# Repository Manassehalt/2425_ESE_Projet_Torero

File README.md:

# 2425_ESE_Projet_Torero

Projet de 3ème année d'ESE réalisé par :  
- **JACQUOT Nolan**  
- **GUIFFAULT Gabriel**  
- **BOULOT Paul**  
- **THOMAR Jean-Philippe**

Ce projet consiste à concevoir un robot autonome de A à Z, combinant électronique et programmation, pour jouer une partie de "chat et souris".

---

## Cahier des charges:
> [!IMPORTANT]
>- Le robot doit être capable de se déplacer sur une table sans tomber (absence de bord et de marquage)
>- Le robot doit être capable de détecter l'autre robot présent sur la table pour le fuir ou le chasser en fonction de son rôle dans la partie.
>- Le robot doit être capable de détecter un contact, même léger, avec le robot adverse et changer son comportement d'un rôle vers l'autre.

Objectif annexe:
- Le robot peut réaliser une odométrie simple pour suivre le bord de table lorsqu'il débute en souris
- Le robot peut réaliser une odométrie simple pour se positionner au centre de la table avant de commencer la traque lorsqu'il débute en chat
- Le robot peut déclencher un brusque changement de direction s'il détecte un robot approchant rapidement en mode souris
- Le robot peut effectuer des prédictions de trajectoire et effectuer des trajectoires de collision en prévision du deplacement adverse en mode chat
- Le robot évite de prendre des directions ou il serait acculé dans un angle de table

## Architecture du système

[Schéma architectural](https://github.com/user-attachments/files/17220902/Schema.architectural.pdf)

1. **Détection de l'environnement** :
   - Les **capteurs de bord** détectent les limites de la table pour prévenir les chutes.
   - Le **LIDAR** identifie et localise les robots adverse.
   - La **centrale inertielle** mesure les mouvements brusques et détecte les chocs pour changer l'état, chat ou souris, du robot.

2. **Traitement des données** :
   - Le **microcontrôleur** centralise les informations provenant des capteurs, analyse les données et décide des actions en fonction du rôle actuel du robot (chat ou souris).

3. **Actionneur** :
   - Les moteurs sont contrôlés via un système de quadrants.
   - Le microcontrôleur ajuste les commandes de mouvement en temps réel (éviter les chutes, fuir ou poursuivre le robot adverse).

4. **Comportement interactif** :
   - Un **switch de comportement** permet de basculer entre les rôles de "chat" et "souris".
   - Les **LED de debug** affichent des informations sur l'état et le rôle actuel du robot.

5. **Alimentation** :
   - Une **batterie** alimente l'ensemble du système.
   - Des convertisseurs intégrés fournissent les tensions nécessaires (7,2 V, 5 V et 3,3 V) pour les différents composants.

## Environnement:

> [!IMPORTANT]
> Table de 200cm x 160cm
> 
> Table sans bords ni marquages!
> 
> Robot assimilable à un cylindre de 17 cm de diametre et 15 cm de hauteur 

##  Liens utiles

### Documentation et ressources :
- [Datasheets](https://github.com/Manassehalt/2425_ESE_Projet_Torero/tree/main/Datasheet)  
- [Liste des tâches](https://github.com/Manassehalt/2425_ESE_Projet_Torero/blob/main/Calculs%20et%20brouillons/Remarque_Sch.md)  
- [BOM (Bill of Materials)](https://github.com/Manassehalt/2425_ESE_Projet_Torero/blob/main/BOM.xlsx)
  
### Design électronique :
- [Fichiers PCB](https://github.com/Manassehalt/2425_ESE_Projet_Torero/tree/main/PCB)  
- [Schémas KiCad](https://github.com/Manassehalt/2425_ESE_Projet_Torero/blob/main/PCB/Projet_torero/Projet_torero.kicad_sch)  

### Code STM32 :
- [Dossier code](https://github.com/Manassehalt/2425_ESE_Projet_Torero/tree/main/Projet_ESE_STM32)  

---

### Aperçu de la carte PCB

[Voir le modèle en 3D](https://github.com/Manassehalt/2425_ESE_Projet_Torero/blob/main/Graphique_Logo/PCB%20carte%203d.PNG)  

### Calculs et développement

- [Dossier calculs](https://github.com/Manassehalt/2425_ESE_Projet_Torero/tree/8892ed05e16a1e8a040fe9dc08f957ab23dc9e8/Calculs%20et%20brouillons)

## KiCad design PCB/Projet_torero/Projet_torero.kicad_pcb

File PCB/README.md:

# Partie PCB - Projet Torero

Ce projet utilise **KiCad** pour la conception des schémas et des PCB. L'architecture électronique est organisée de manière hiérarchique pour une gestion claire.

---

##  Organisation des fichiers
La hiérarchie des schémas est structurée en plusieurs pages, chacune correspondant à une fonctionnalité spécifique :

- **Page principale (Racine)** : Vue d'ensemble de l'architecture.
- **STM32 (Page 2)** : Microcontrôleur central et ses connexions.
- **Puissance (Page 3)** : Alimentation et distribution des tensions.
  - Contrôle des moteurs gauche et droit.
- **Capteurs (Page 4)** : Intégration des capteurs, tels que le Lidar, l'accéléromètre, et les détecteurs de bord.
- **Alimentation (Page 5)** : Régulateurs pour les tensions de 3,3 V et 5 V.

---

## Composants principaux

### **Microcontrôleur STM32** (Page 2)
- **STM32G431CBU** : Le contrôle central du système.
- Connexions UART, SPI, et GPIO configurées pour communiquer avec les capteurs, moteurs, et périphériques.

### **Puissance et Moteurs** (Pages 3, 6, 7)
- **Drivers moteurs ZXBM5210-SP** pour le contrôle des moteurs gauche et droit.
- Les connecteurs moteurs incluent des signaux pour les encodeurs et les commandes de direction.

### **Capteurs** (Page 4)
- **Lidar** : Connecté via UART pour les mesures de distance et d'obstacles.
- **Accéléromètre ADXL343** : Géré via SPI pour les données inertiales.
- **Capteurs de bord QRD1114** : Utilisés pour détecter les limites de la table.

### **Alimentation** (Page 5)
- Régulateur **5 V** : MP14755.
- Régulateur **3,3 V** : BU33SD5WG-TR.
- Connecteurs pour la batterie 7,2 V et le switch ON/OFF.

---

## Fonctionnalités de conception
- **Hiérarchie des schémas** : Organisation pour une meilleure lisibilité.
- **Test points** : Ajoutés pour faciliter les mesures et le debug sur le PCB avec l'ocsilloscope.

---

## Aperçu des schémas

### Vue principale

### STM32

### Puissance

Voici le schéma d'un des moteurs :

### Capteurs

Voici le schéma d'un des caepterus de bord :

### Alimentation

---

## Rutage du PCB :

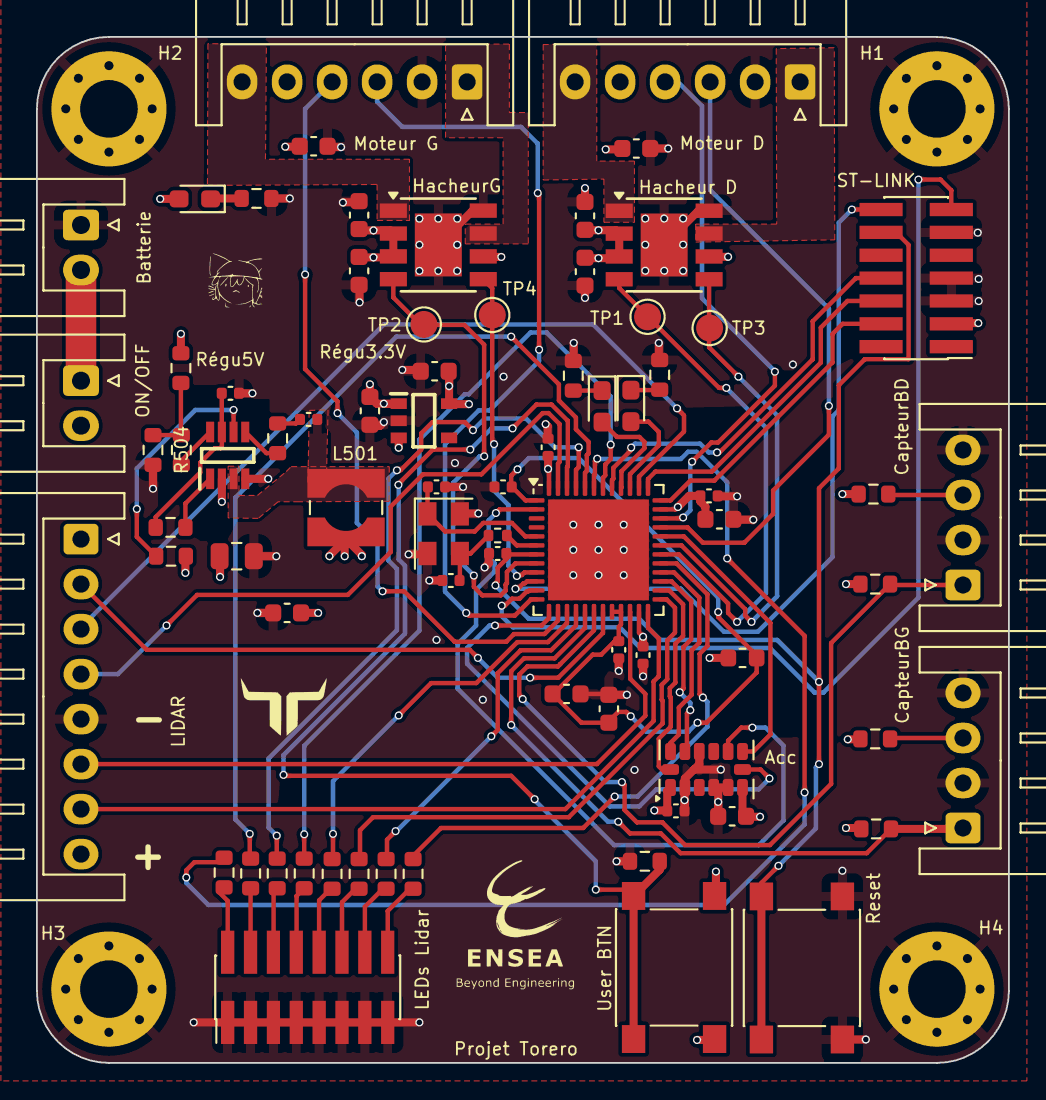
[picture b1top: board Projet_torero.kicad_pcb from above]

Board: 4 copper layers, 54.0 x 57.0 mm, 79 parts (0 on the bottom side), 72 nets.

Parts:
10k201: 10k; R_0603_1608Metric
Acc: ADXL343; LGA-14_3x5mm_P0.8mm_LayoutBorder1x6y
Batterie: Conn_01x02; JST_XH_S2B-XH-A_1x02_P2.50mm_Horizontal
C201, C202: 20p; C_0402_1005Metric
C203, C204, C206, C207, C208, C402, C502, C503: 100n; C_0402_1005Metric
C205, C210, C401, C505, C506, C601, C603, C701, C703: 1u; C_0603_1608Metric
C209: 4n7; C_0603_1608Metric
C211: 10n; C_0402_1005Metric
C501: 22u; C_0805_2012Metric
C504: 47u; C_0603_1608Metric
C602, C702: 10u; C_0603_1608Metric
CapteurBD: JST_XH_S4B-XH-A_1x04_P2.50mm_Horizontal
CapteurBG: JST_XH_S4B-XH-A_1x04_P2.50mm_Horizontal
D1, D202: Red; LED_0603_1608Metric_Pad1.05x0.95mm_HandSolder
D201: Green; LED_0603_1608Metric_Pad1.05x0.95mm_HandSolder
H1, H2, H3, H4: MountingHole_Pad; MountingHole_3.2mm_M3_Pad_Via
Hacheur D: ZXBM5210-SP; Diodes_SO-8EP
HacheurG: ZXBM5210-SP; Diodes_SO-8EP
L202: L; L_0603_1608Metric
L501: 4u7; L_Wuerth_WE-TPC-3816
LEDs Lidar: Conn_02x08_Odd_Even; PinHeader_2x08_P1.27mm_Vertical_SMD
LIDAR: Conn_01x08; JST_XH_S8B-XH-A_1x08_P2.50mm_Horizontal
Moteur D: Conn_01x06; JST_XH_S6B-XH-A_1x06_P2.50mm_Horizontal
Moteur G: Conn_01x06; JST_XH_S6B-XH-A_1x06_P2.50mm_Horizontal
ON/OFF: Conn_01x02; JST_XH_S2B-XH-A_1x02_P2.50mm_Horizontal
R201: 10; R_0402_1005Metric
R202: 120; R_0603_1608Metric
R203, R314: 140; R_0603_1608Metric
R204, R205, R206, R207, R208, R209, R210, R211: 1k; R_0603_1608Metric
R501, R502: 100k; R_0603_1608Metric
R503: 20; R_0603_1608Metric
R504: 16k; R_0603_1608Metric
R505: 40k2; R_0603_1608Metric
R506: 7k68; R_0603_1608Metric
R801, R901: 300; R_0603_1608Metric
R802, R902: 15k3; R_0603_1608Metric
Reset: SW_Push; SW_Push_1P1T_NO_6x6mm_H9.5mm
Régu3.3V: BU33SD5WG-TR; SOT95P280X125-5N
Régu5V: MP1475SGJ-P; SOT65P280X100-8N
ST-LINK: Conn_02x07_Odd_Even; PinHeader_2x07_P1.27mm_Vertical_SMD
SW201: SW_Push; SW_Push_1P1T_NO_6x6mm_H9.5mm
TP1, TP2, TP3, TP4: TestPoint; TestPoint_Pad_D1.5mm
U201: STM32G431CBUx; QFN-48-1EP_7x7mm_P0.5mm_EP5.6x5.6mm
Y201: Crystal_GND24_Small; Crystal_SMD_EuroQuartz_MT-4Pin_3.2x2.5mm

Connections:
7.2V: C501.1, C601.2, C602.1, C701.2, C702.1, Hacheur D.2 (VM), Hacheur D.3 (VDD), Hacheur D.6 (VREF), HacheurG.2 (VM), HacheurG.3 (VDD), HacheurG.6 (VREF), ON/OFF.2, R501.1, Régu5V.2 (IN)
+3.3V: Acc.1 (Vdd_I/O), Acc.6 (Vs), C206.1, C207.1, C208.1, C209.1, C401.1, C402.2, C506.2, C603.2, C703.2, D201.2 (A), L202.1, Moteur D.5, Moteur G.5, R801.1, R802.2, R901.1, R902.2, Régu3.3V.5 (VOUT), ST-LINK.3, SW201.2, U201.23 (VDD), U201.35 (VDD), U201.48 (VDD)
+5V: C504.1, C505.1, L501.2, LIDAR.8, R505.1, Régu3.3V.1 (VIN), Régu3.3V.3 (STBY)
/ALIMENTATION/Sortie Régulateur 5V: C503.2, L501.1, Régu5V.3 (SW)
/CAPTEURS/ANALOG_OUTPUT_CAPT_BORD_D: CapteurBD.1, R901.2, U201.18 (PB1)
/CAPTEURS/ANALOG_OUTPUT_CAPT_BORD_G: CapteurBG.1, R801.2, U201.17 (PB0)
/CAPTEURS/CS_ACC: Acc.7 (~CS), U201.13 (PA5)
/CAPTEURS/DEV_EN_LIDAR: LIDAR.3, U201.38 (PA15)
/CAPTEURS/INT1_ACC: Acc.8 (INT1), U201.32 (PA10)
/CAPTEURS/INT2_ACC: Acc.9 (INT2), U201.2 (PC13)
/CAPTEURS/M_EN_LIDAR: LIDAR.2, U201.19 (PB2)
/CAPTEURS/M_SCTR_LIDAR: LIDAR.4, U201.47 (PB9)
/CAPTEURS/Rx_LIDAR: LIDAR.6, U201.22 (PB10)
/CAPTEURS/SCLK_ACC: Acc.14 (SCL/SCLK), U201.26 (PB13)
/CAPTEURS/SDI_ACC: Acc.13 (SDA/SDI/SDIO), U201.28 (PB15)
/CAPTEURS/SDO_ACC: Acc.12 (SDO/ADDR), U201.27 (PB14)
/CAPTEURS/Tx_LIDAR: LIDAR.7, U201.24 (PB11)
/PUISSANCE/EncodeurA_Droite: Moteur G.3, U201.12 (PA4)
/PUISSANCE/EncodeurA_Gauche: Moteur D.3, U201.33 (PA11)
/PUISSANCE/EncodeurB_Droite: Moteur G.4, U201.14 (PA6)
/PUISSANCE/EncodeurB_Gauche: Moteur D.4, U201.34 (PA12)
/PUISSANCE/FWDD: HacheurG.4 (FWD), TP2.1, U201.8 (PA0)
/PUISSANCE/FWDG: Hacheur D.4 (FWD), TP1.1, U201.30 (PA8)
/PUISSANCE/Moteur1/Commande moteur: HacheurG.7 (OUT2), Moteur G.1
/PUISSANCE/Moteur1/Connecteur Moteur: HacheurG.1 (OUT1), Moteur G.6
/PUISSANCE/Moteur/Commande moteur: Hacheur D.7 (OUT2), Moteur D.1
/PUISSANCE/Moteur/Connecteur Moteur: Hacheur D.1 (OUT1), Moteur D.6
/PUISSANCE/REVD: HacheurG.5 (REV), TP4.1, U201.9 (PA1)
/PUISSANCE/REVG: Hacheur D.5 (REV), TP3.1, U201.31 (PA9)
/STM32/USER_BTN: 10k201.2, SW201.1, U201.46 (PB8)
GND: 10k201.1, Acc.2 (GND), Acc.4 (GND), Acc.5 (GND), Acc.11 (RES), Batterie.1, C201.1, C202.2, C203.2, C204.2, C205.2, C206.2, C207.2, C208.2, C209.2, C210.2, C211.2, C401.2, C402.1, C501.2, C502.2, C504.2, C505.2, C506.1, C601.1, C602.2, C603.1, C701.1, C702.2, C703.1, CapteurBD.2, CapteurBD.4, CapteurBG.2, CapteurBG.4, H1.1, H2.1, H3.1, H4.1, Hacheur D.8 (GND), Hacheur D.9 (GND), HacheurG.8 (GND), HacheurG.9 (GND), LEDs Lidar.1, LEDs Lidar.3, LEDs Lidar.5, LEDs Lidar.7, LEDs Lidar.9, LEDs Lidar.11, LEDs Lidar.13, LEDs Lidar.15, LIDAR.5, Moteur D.2, Moteur G.2, R202.1, R203.1, R314.1, R506.2, Reset.1, Régu3.3V.2 (GND), Régu5V.4 (GND), ST-LINK.5, ST-LINK.7, ST-LINK.11, U201.49 (VSS), Y201.2, Y201.4
LED_E: R205.1, U201.44 (PB6)
LED_N: R204.1, U201.43 (PB5)
LED_NE: R208.1, U201.15 (PA7)
LED_NW: R209.1, U201.25 (PB12)
LED_S: R206.1, U201.45 (PB7)
LED_SE: R210.1, U201.16 (PC4)
LED_SW: R211.1, U201.29 (PC6)
LED_W: R207.1, U201.42 (PB4)
NRST: C203.1, Reset.2, ST-LINK.12, U201.7 (PG10)
unnamed: C201.2, R201.2, Y201.3
unnamed: C503.1, R503.1
unnamed: D1.1 (K), R314.2
unnamed: D201.1 (K), R202.2
unnamed: D202.1 (K), R203.2
unnamed: R503.2, Régu5V.5 (BST)
unnamed: R501.2, Régu5V.6 (EN/SYNC)
unnamed: R504.2, Régu5V.8 (FB)
unnamed: R502.2, Régu5V.1 (PG)
unnamed: C502.1, R502.1, Régu5V.7 (VCC)
unnamed: LEDs Lidar.2, R204.2
unnamed: LEDs Lidar.4, R205.2
unnamed: LEDs Lidar.6, R206.2
unnamed: LEDs Lidar.8, R207.2
unnamed: LEDs Lidar.10, R208.2
unnamed: LEDs Lidar.12, R209.2
unnamed: LEDs Lidar.14, R210.2
unnamed: LEDs Lidar.16, R211.2
unnamed: Batterie.2, ON/OFF.1
unnamed: CapteurBG.3, R802.1
unnamed: CapteurBD.3, R902.1
unnamed: R504.1, R505.2, R506.1
unnamed: C202.1, U201.5 (PF0), Y201.1
unnamed: R201.1, U201.6 (PF1)
unnamed: C204.1, C205.1, C210.1, C211.1, L202.2, U201.1 (VBAT), U201.20 (VREF+), U201.21 (VDDA)
STATUS_LED: D202.2 (A), U201.39 (PC10)
STATUS_LED_Debug: D1.2 (A), U201.40 (PC11)
SWCLK: ST-LINK.6, U201.37 (PA14)
SWDIO: ST-LINK.4, U201.36 (PA13)
SWO: ST-LINK.8, U201.41 (PB3)
VCP_RX: ST-LINK.13, U201.11 (PA3)
VCP_TX: ST-LINK.14, U201.10 (PA2)

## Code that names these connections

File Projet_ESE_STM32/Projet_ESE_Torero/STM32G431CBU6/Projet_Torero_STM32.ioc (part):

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Mcu.Name=STM32G431C(6-8-B)Ux
Mcu.Package=UFQFPN48
Mcu.UserName=STM32G431CBUx
PA0.Signal=S_TIM2_CH1
PA1.Signal=S_TIM2_CH2
PA10.GPIOParameters=GPIO_PuPd,GPIO_Label
PA10.GPIO_Label=INT1_ACC
PA10.GPIO_PuPd=GPIO_NOPULL
PA10.Signal=GPXTI10
PA11.Signal=S_TIM4_CH1
PA12.Signal=S_TIM4_CH2
PA13.Mode=Trace_Asynchronous_SW
PA13.Signal=SYS_JTMS-SWDIO
PA14.Mode=Trace_Asynchronous_SW
PA14.Signal=SYS_JTCK-SWCLK
PA15.GPIOParameters=PinState,GPIO_Label
PA15.GPIO_Label=DEV_EN_LIDAR
PA15.PinState=GPIO_PIN_SET
PA15.Signal=GPIO_Output
PA2.Mode=Asynchronous
PA2.Signal=USART2_TX
PA3.Mode=Asynchronous
PA3.Signal=USART2_RX
PA4.Signal=S_TIM3_CH2
PA5.GPIOParameters=PinState,GPIO_Label
PA5.GPIO_Label=CS_ACC
PA5.PinState=GPIO_PIN_SET
PA5.Signal=GPIO_Output
PA6.Signal=S_TIM3_CH1
PA7.GPIOParameters=GPIO_Label
PA7.GPIO_Label=LED_NE
PA7.Signal=GPIO_Output
PA8.Signal=S_TIM1_CH1
PA9.Signal=S_TIM1_CH2
PB0.GPIOParameters=GPIO_Label,GPIO_ModeDefaultEXTI
PB0.GPIO_Label=CAPTEUR_G
PB0.GPIO_ModeDefaultEXTI=GPIO_MODE_IT_RISING_FALLING
PB0.Signal=GPXTI0
PB1.GPIOParameters=GPIO_Label,GPIO_ModeDefaultEXTI
PB1.GPIO_Label=CAPTEUR_D
PB1.GPIO_ModeDefaultEXTI=GPIO_MODE_IT_RISING_FALLING
PB1.Signal=GPXTI1
PB10.GPIOParameters=GPIO_Label
PB10.GPIO_Label=USART3_TX_LIDAR
PB10.Mode=Asynchronous
PB10.Signal=USART3_TX
PB11.GPIOParameters=GPIO_Label
PB11.GPIO_Label=USART3_RX_LIDAR
PB11.Mode=Asynchronous
PB11.Signal=USART3_RX
PB12.GPIOParameters=GPIO_Label
PB12.GPIO_Label=LED_NW
PB12.Signal=GPIO_Output
PB13.GPIOParameters=GPIO_Label
PB13.GPIO_Label=SPI2_SCK_TO_SCLK_ACC
PB13.Mode=Full_Duplex_Master
PB13.Signal=SPI2_SCK
PB14.GPIOParameters=GPIO_Label
PB14.GPIO_Label=SPI2_MISO_TO_SDO_ACC
PB14.Mode=Full_Duplex_Master
PB14.Signal=SPI2_MISO
PB15.GPIOParameters=GPIO_Label
PB15.GPIO_Label=SPI2_MOSI_TO_SDI_ACC
PB15.Mode=Full_Duplex_Master
PB15.Signal=SPI2_MOSI
PB2.GPIOParameters=PinState,GPIO_Label
PB2.GPIO_Label=M_EN_LIDAR
PB2.PinState=GPIO_PIN_SET
PB2.Signal=GPIO_Output
PB3.Mode=Trace_Asynchronous_SW
PB3.Signal=SYS_JTDO-SWO
PB4.GPIOParameters=GPIO_Label
PB4.GPIO_Label=LED_W
PB4.Signal=GPIO_Output
PB5.GPIOParameters=GPIO_Label
PB5.GPIO_Label=LED_N
PB5.Signal=GPIO_Output
PB6.GPIOParameters=GPIO_Label
PB6.GPIO_Label=LED_E
PB6.Signal=GPIO_Output
PB7.GPIOParameters=GPIO_Label
PB7.GPIO_Label=LED_S
PB7.Signal=GPIO_Output
PB8-BOOT0.Signal=GPXTI8
PB9.GPIOParameters=GPIO_Label
PB9.GPIO_Label=TIM4_CH4_M_SCTR_LIDAR
PB9.Signal=S_TIM4_CH4
PC10.GPIOParameters=GPIO_Label
PC10.GPIO_Label=Status_LED
PC10.Signal=GPIO_Output
PC11.GPIOParameters=GPIO_Label
PC11.GPIO_Label=Status_LED_debbug
PC11.Signal=GPIO_Output
PC13.GPIOParameters=GPIO_PuPd,GPIO_Label
PC13.GPIO_Label=INT2_ACC
PC13.GPIO_PuPd=GPIO_NOPULL
PC13.Signal=GPXTI13
PC4.GPIOParameters=GPIO_Label
PC4.GPIO_Label=LED_SE
PC4.Signal=GPIO_Output
PC6.GPIOParameters=GPIO_Label
PC6.GPIO_Label=LED_SW
PC6.Signal=GPIO_Output
PF0-OSC_IN.Mode=HSE-External-Oscillator
PF0-OSC_IN.Signal=RCC_OSC_IN
PF1-OSC_OUT.Mode=HSE-External-Oscillator
PF1-OSC_OUT.Signal=RCC_OSC_OUT
PG10-NRST.GPIOParameters=GPIO_Label
PG10-NRST.GPIO_Label=RESET
PG10-NRST.Signal=GPIO_Input
RCC.HSE_VALUE=16000000
RCC.SYSCLKFreq_VALUE=16000000
RCC.SYSCLKSource=RCC_SYSCLKSOURCE_HSE
board=custom

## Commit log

2024-09-11 BOM added
2024-09-11 Modif BOM
2024-09-11 Add Item Column
2024-09-11 schéma archi added
2024-09-11 modif datasheets quartz
2024-09-11 Filling BOM file
2024-09-18 Rename 0900766b81582941.pdf to batterie.pdf
2024-09-18 Rename 3820205(quartz).pdf to 16MHz_quartz.pdf
2024-09-18 Rename BU18SD5WG.PDF to Regulateur3V3.PDF
2024-09-18 Rename MP1475S.pdf to Regulateur5V.pdf
2024-09-18 Rename FIT0520_Web.pdf to Motor.pdf
2024-09-18 Rename adxl343.pdf to Accelerometer.pdf
2024-09-18 Rename ZXBM5210.PDF to DriverMotor.PDF
2024-09-18 add kicad
2024-09-18 Rename QRD1113.PDF to CapteurBord.PDF
2024-09-18 ssh key
2024-09-18 kicad capteurs modif
2024-09-18 modif capteurs
2024-09-25 Ajout info PCB 25/09
2024-09-25 Rajouté la STM32
2024-09-25 add kicad puissance
2024-09-25 modif kicad capteur
2024-09-25 modif kicad capteur + excel liens/sources
2024-10-01 Mis à jour, manque l'interupteur ON/OFF
2024-10-01 Inversion pins lidar
2024-10-01 Rajout interupteur ON/OFF
2024-10-01 Remarque pour amélioration schématique
2024-10-01 Remarque pour amélioration schématique v2
2024-10-01 Corriger les erreurs de la STM
2024-10-01 modification moteurs et alim
2024-10-01 checklist
2024-10-01 modif capa moteur
2024-10-01 modif alim
2024-10-01 modif alim fin ?
2024-10-01 modif valeur composants passifs
2024-10-02 suivi modif remarques
2024-10-02 Mit à jour les encodeurs
2024-10-02 modif labels hiérarchiques
2024-10-02 Update README.md
    Rajout de lien et une courte introduction
2024-10-02 add symbole capteur de bord
2024-10-02 Update README.md
    rajout des datasheets
2024-10-02 ajout nouvelles feuilles capteurs bords
2024-10-02 ajout modif capteurs de bord
2024-10-02 ajout valeur capa accelerometer
2024-10-02 Update README.md
    rajout de mise en page/hierarchie
2024-10-02 modif capteur
2024-10-02 review sch
2024-10-02 review sch 2
2024-10-02 review sch après vérif prof
2024-10-02 changement pins STlink
2024-10-02 Update README.md
    Cahier des charges
2024-10-02 add calcul qrd1113
2024-10-02 Update Remarque_Sch.txt
    mise en forme
2024-10-02 changement schéma
2024-10-08 Empreinte Switch ON/OFF
2024-10-08 Delete LIB_BU33SD5WG-TR.zip
    erreur
2024-10-08 LIBRAIRIE BU33SD5WG
2024-10-08 Librairies
    Ajoute des librairies de composants
2024-10-08 Projet STM32
2024-10-08 Liste empreintes
    passive R and C
2024-10-08 Ajout capteur bordure
2024-10-08 modif capteur de bord
2024-10-08 unzip proj stm
2024-10-08 maj pin STM
2024-10-08 Ajouté les empreintes
2024-10-08 Re-Push pour les empreintes et le PCB
2024-10-08 modif placement composant
2024-10-09 Update README.md
    Rajout des dossier software
2024-10-09 Refait l'alimentation
2024-10-09 modif routing
2024-10-09 Mis à jour des composants
2024-10-09 Ajout Switch ON/OFF sur carte
2024-10-09 Nouvelle version avec Empreinte correcte
2024-10-09 Placement des composants
2024-10-09 rangement dossiers
2024-10-09 Correction Prof
2024-10-09 Placement des composant "terminé"
2024-10-09 changement pin usart2
2024-10-09 rectification erreur pin usart2
2024-10-14 add logo ensea
2024-10-14 routage à valider
2024-10-16 Corriger les erreurs
2024-10-16 changement calculs capteur bord + modif bom
2024-10-16 Correction du PCB pour prof
2024-10-16 Update Remarque_Sch.txt
    remarque routage
2024-10-16 ajout fichier meca
2024-10-16 Correction suggestion prof
2024-10-22 png architecture
2024-10-22 Update README.md
    rajout du visuel
2024-10-22 Update README.md
    mise en page
2024-10-22 Modif BOM + ajout du bon de commande
2024-10-22 Confirmation PCB
    Il manque juste a finir le texte et mettre les logos de l'ENSEA et du groupe TORERO
2024-10-22 Image 3d PCB
2024-10-22 Update README.md
    add serigraphie
2024-10-22 Update README.md
    le logo, le logo !!!
2024-10-22 fichier gerber et ajout logo ensea
2024-10-23 ajout cornes taureau
2024-10-23 Update README.md
    j'ai fix les image du read me
2024-10-23 Rajouté logo
2024-10-23 Ajoute du Gerber pour la fabrication
2024-10-23 Corrige petite erreur texte
2024-10-23 Changer le Gerber
2024-10-23 add projet stm pour test lidar
2024-10-23 Adapté la taille des pastilles
2024-10-23 Update Remarque_Sch.txt
    nouvelle task
2024-10-23 Update README.md
    oudated link fixed
2024-10-23 maj meca robot
2024-11-05 Update and rename Remarque_Sch.txt to Remarque_Sch.md
    md is life
2024-11-05 Update Remarque_Sch.md
    tentatives liste cliquables
2024-11-26 modif lidar test
2024-11-26 Schéma archi clean
2024-11-27 fichier meca
2024-11-27 add driver lidar
2024-11-28 aucune modif
2024-12-03 driver lidar
2024-12-04 modif driver lidar
2024-12-04 gen fichier periph
2024-12-10 lidar
2024-12-11 Test moteur
2024-12-11 Corrigé l'ACC
2024-12-11 freertos
2024-12-17 proto fonctions
2025-01-07 tache accelero
2025-01-09 capteur bord ok
2025-01-09 is not dropping
2025-01-09 is not dropping again
2025-01-09 add test lidar
2025-01-09 test lidar
2025-01-10 project stm
2025-01-10 maj delay
2025-01-11 maj task motor and edge
2025-01-13 maj freertos
2025-01-14 changement define dans les drivers
2025-01-14 changement commentaire
2025-01-15 commentaires driver lidar
2025-01-15 Update main.c
    rajout des comportements de traque et fuite prise en compte des distances et de l'angle
2025-01-15 mise en commentaire TaskMOTOR évoluée
2025-01-15 Update README.md
    ajout d'un descriptif de TaskMOTOR si le lidar marche
